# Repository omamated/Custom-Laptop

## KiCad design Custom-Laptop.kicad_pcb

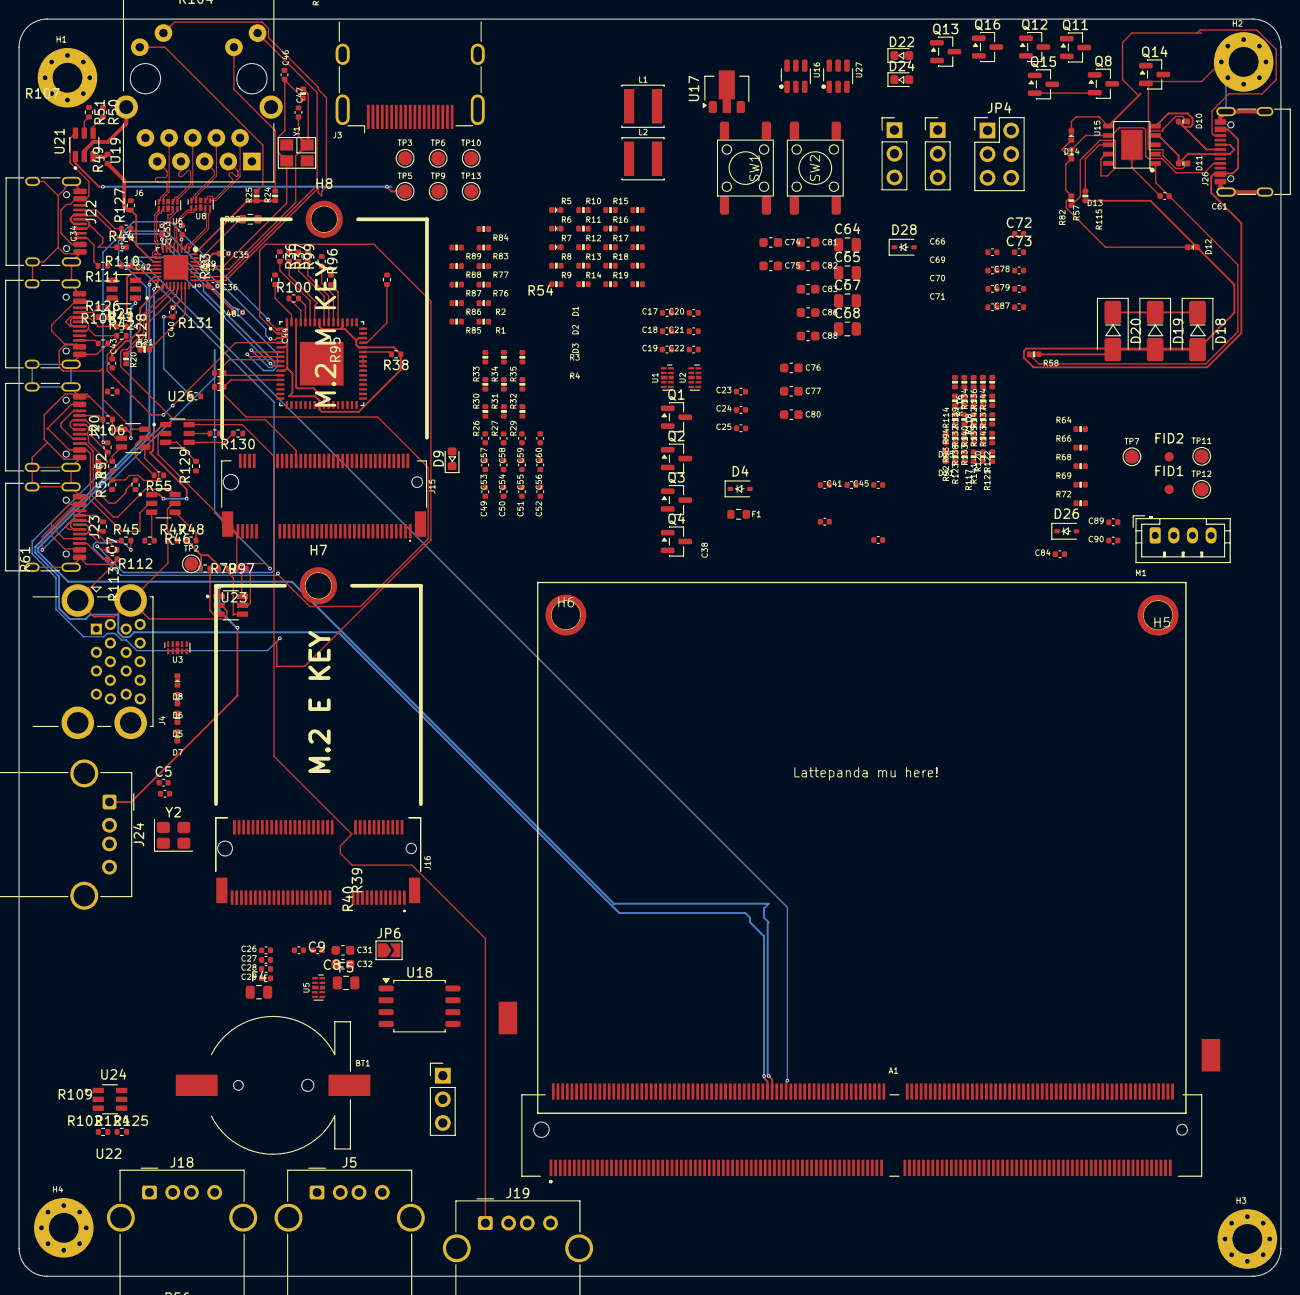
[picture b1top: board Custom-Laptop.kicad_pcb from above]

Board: 4 copper layers, 135.5 x 135.0 mm, 304 parts (0 on the bottom side), 247 nets.

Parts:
A1: LattePanda_Module_Gen1; DDR4_SODIMM_260P_8.0H_STD
BT1: Battery_Cell; Battery_Holder_CR1220_S8411-45R
C5: 1.0µF; C_0402_1005Metric
C7, C9: 27pF; C_0402_1005Metric
C8: 100nF; C_0402_1005Metric
C17, C18, C19, C20, C21, C22, C23, C24, C25, C26, C27, C28, C29, C33, C34, C35, C36, C37, C38, C39, C40, C41, C42, C43, C45, C48, C52, C54, C58, C60, C70, C71, C78, C79, C84: 100nF/16V; C_0402_1005Metric
C31, C32, C74, C75, C76, C77, C80, C81, C82, C83: 22uF/10V; C_0603_1608Metric
C44, C51, C53, C57, C59, C87, C89: 10uF/10V; C_0402_1005Metric
C46, C47, C72, C73: 12pF/50V; C_0402_1005Metric
C49, C50, C55, C56: 220nF/16V; C_0402_1005Metric
C61, C66, C69: 1uF/16V; C_0402_1005Metric
C64, C65, C67, C68: 22uF/25V; C_0805_2012Metric
C86, C88: 2.2uF/50V; C_0603_1608Metric
C90: 100nF/50V; C_0402_1005Metric
D1, D2, D3, D5, D6, D7, D8, D10, D11, D13, D14, D21, D25: 0402ESDA-05N; D_0402_1005Metric
D4, D26, D28: 1N5819WS; D_SOD-323
D9, D24: LED_G; LED_0603_1608Metric
D12: PESD24VS1UL-N; D_0402_1005Metric
D18, D19, D20: SS54; D_SMA
D22: LED_R; LED_0603_1608Metric
F1: 6V/50mA; R_0603_1608Metric
F4, F5: 6V/2A; Fuse_0805_2012Metric
FID1, FID2: Fiducial; Fiducial_1mm_Mask2mm
H1, H2, H3, H4: MountingHole_Pad; MountingHole_3.2mm_M3_Pad_Via
H5, H6: MountingHole_Pad; MountingHole_3mm_M2_Pad_TopOnly
H7, H8: MountingHole_M2.0; MountingHole_2.7mm_M2_Pad_TopOnly
J1: Conn_01x03_Pin; PinHeader_1x03_P2.54mm_Vertical
J3: HDMI_A; HDMI_A_Molex_208658-1001_Horizontal
J4: USB3_A_Stacked; USB3_A_Molex_48406-0001_Horizontal_Stacked
J5, J18, J19, J24: USB_A; USB_A_Molex_67643_Horizontal
J6: RJ45_RB1-125B8G1A; RJ45_UDE_RB1-125B8G1A
J15: Bus_M.2_Socket_M; PCIe_M.2_Connectors_P=0.5mm_H=4.2mm_KeyM
J16: Bus_M.2_Socket_E; PCIe_M.2_Connectors_P=0.5mm_H=4.2mm_KeyE
J20, J21, J22, J23: USB_C_Receptacle_USB2.0_14P; USB_C_Receptacle_HRO_TYPE-C-31-M-12
J26: USB_C_Receptacle_USB2.0; USB_C_Receptacle_G-Switch_GT-USB-7010ASV
JP1, JP5: Jumper_3_Bridged12; PinHeader_1x03_P2.54mm_Vertical
JP4: PinHeader_2x03_P2.54mm_Vertical
JP6: SolderJumper_2_Open; SolderJumper-2_P1.3mm_Open_TrianglePad1.0x1.5mm
L1, L2: 2.2uH/4.3A; L_Sunlord_SWPA4020S
M1: Fan_4pin; JST_PH_B4B-PH-K_1x04_P2.00mm_Vertical
Q1, Q8, Q11, Q12, Q13, Q14, Q15: 2N7002; SOT-23
Q2, Q3, Q4: 2SK3018; SOT-23
Q16: AO3407; SOT-23
R1, R11, R58, R92, R121, R122: 1K/1%; R_0402_1005Metric
R2, R20, R21, R34, R35, R57, R83, R115, R123, R136, R140, R143, R144: 10K/1%; R_0402_1005Metric
R3, R5, R15, R18, R19, R30, R117, R133: 2.2K/1%; R_0402_1005Metric
R4, R23, R118: 1M/1%; R_0402_1005Metric
R6, R66, R68, R137: 21.5K/1%; R_0402_1005Metric
R7, R8, R9, R10, R13, R14, R16, R17, R24, R25, R132: 470R/1%; R_0402_1005Metric
R12, R26, R27, R29, R31, R32, R33, R84, R85, R86, R87, R88, R89: 0R/1%; R_0402_1005Metric
R22: 2.49K/1%; R_0603_1608Metric
R36, R37, R39, R40, R41, R42, R43, R44, R45, R54, R61, R62, R95, R96, R98, R99: 22Ω; R_0402_1005Metric
R38, R104: 10kΩ; R_0402_1005Metric
R46, R48, R49, R50, R52, R53, R56, R79, R102, R124, R126, R127, R129, R130: 100kΩ; R_0402_1005Metric
R47, R51, R55, R97, R125, R128, R131: 16.2kΩ; R_0402_1005Metric
R64, R72, R138: 4.7K/1%; R_0402_1005Metric
R69, R93, R94, R114, R134, R139, R142: 100R/1%; R_0402_1005Metric
R76, R77, R116, R120: 100K/1%; R_0402_1005Metric
R82: 56K/1%; R_0402_1005Metric
R100: 1MΩ; R_0402_1005Metric
R101: 12kΩ ±1%; R_0402_1005Metric
R106, R107, R108, R109, R110, R111, R112, R113: 5.1kΩ; R_0402_1005Metric
R135: 75K/1%; R_0402_1005Metric
R141: 200R/1%; R_0402_1005Metric
SW1, SW2: SW_Push; SW_Push_6x6x6
TP2, TP3, TP5, TP6, TP7, TP9, TP10, TP11, TP12, TP13: TestPoint; TestPoint_Pad_D1.5mm
U1, U2: TPAZ1023-04F; Diodes_UDFN-10_1.0x2.5mm_P0.5mm
U3, U5, U7, U8: ULC0524P; Diodes_UDFN-10_1.0x2.5mm_P0.5mm
U6: RTL8111H-CG-RH; QFN-32-1EP_4x4mm_P0.4mm_EP2.65x2.65mm
U14: USB2517-JZX; QFN50P900X900X100-65N
U15: CH224K; ESSOP-10-1EP_3.9x5mm_P1.0mm_EP3.2x2.3
U16, U27: SY8253ADC; TSOT-23-6
U17: HM7533HBPR; SOT-89-3
U18: W25Q128JVS; SOIC-8_5.3x5.3mm_P1.27mm
U19, U21, U22, U23, U24, U25, U26: TPS2553DBVR; SOT95P280X145-6N
Y1: 25MHz; Crystal_SMD_3225-4Pin_3.2x2.5mm
Y2: Crystal; Crystal_SMD_3225-4Pin_3.2x2.5mm

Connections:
5V_HDMI_VCC: C25.1, D4.1 (K), F1.1, R15.1, R18.1
+1V0: C33.2, C34.2, C35.2, C36.2, C40.2, C44.2, U6.3 (AVDD10), U6.8 (AVDD10), U6.22 (DVDD10), U6.24 (REGOUT), U6.30 (AVDD10)
+1V8: C5.2, U14.25 (VDD18), U14.62 (VDD18PLL)
+3V3: C8.1, C37.2, C41.2, C45.2, C51.2, C52.2, C53.2, C54.2, C57.2, C58.2, C59.2, C60.2, C73.1, C75.2, C77.2, C79.1, C81.2, C83.2, J15.2 (3.3V), J15.4 (3.3V), J15.12 (3.3V), J15.14 (3.3V), J15.16 (3.3V), J15.18 (3.3V), J15.70 (3.3V), J15.72 (3.3V), J15.74 (3.3V), J16.2 (3.3V), J16.4 (3.3V), J16.72 (3.3V), J16.74 (3.3V), L2.2, Q1.1 (G), Q2.1 (G), Q3.1 (G), R3.1, R4.1, R5.1, R20.1, R21.1, R24.2, R25.2, R30.2, R34.2, R35.1, R38.1, R46.1, R48.1, R49.1, R50.1, R52.1, R53.1, R56.1, R64.1, R79.1, R102.1, R124.1, R126.1, R127.1, R129.1, R130.1, R137.2, R140.2, R141.1, R143.2, TP6.1 (1_1), U6.11 (AVDD33), U6.23 (VDDREG), U6.32 (AVDD33), U14.5 (VDDA33), U14.10 (VDDA33), U14.24 (VDD33CR), U14.44 (VBUS_DET), U14.46 (VDD33), U14.52 (VDDA33), U14.57 (VDDA33), U14.64 (VDD33PLL)
+3V3_ROM: C88.1, C89.2, C90.2, D28.1 (K), R2.2, R83.2, R117.2, R118.1, R120.1, R132.1, R133.2, TP13.1 (1_1), U17.3 (VOUT), U18.8 (VCC)
+5V: C31.2, C32.2, C72.1, C74.2, C76.2, C78.1, C80.2, C82.2, D4.2 (A), F4.1, F5.1, J24.1 (VBUS), L1.2, Q16.2 (S), R135.2, R144.2, TP5.1 (1_1), U19.1 (IN), U21.1 (IN), U22.1 (IN), U23.1 (IN), U24.1 (IN), U25.1 (IN), U26.1 (IN)
+5V_FAN: C84.1, D26.1 (K), M1.2 (+), Q16.3 (D), R72.1
+15V: D12.1 (K), D18.2 (A), D19.2 (A), D20.2 (A), J26.A4 (VBUS), J26.A9 (VBUS), J26.B4 (VBUS), J26.B9 (VBUS), R57.1, R58.1, TP3.1 (1_1)
+BATT: A1.115 (VBAT), R1.1
/Fan_Temp/FAN_1_PWM: A1.2 (FAN_CTL2), R64.2, R69.1, TP12.1 (1_1)
/Fan_Temp/FAN_1_TAC: A1.4 (FAN_TAC2), R66.1, R68.2, TP11.1 (1_1)
/Gigabit Ethernet/GbE_PCIe_CLK+: A1.94 (REFCLK4+), U6.15 (REFCLK_P)
/Gigabit Ethernet/GbE_PCIe_CLK-: A1.96 (REFCLK4-), U6.16 (REFCLK_N)
/Gigabit Ethernet/GbE_PCIe_RX+: A1.64 (HSIO6_RXP), C43.2
/Gigabit Ethernet/GbE_PCIe_RX-: A1.66 (HSIO6_RXN), C39.2
/Gigabit Ethernet/GbE_PCIe_TX+: A1.61 (HSIO6_TXP), C42.2
/Gigabit Ethernet/GbE_PCIe_TX-: A1.63 (HSIO6_TXN), C38.2
/Gigabit Ethernet/HSI+: C42.1, U6.13 (HSIP)
/Gigabit Ethernet/HSI-: C38.1, U6.14 (HSIN)
/Gigabit Ethernet/HSO+: C43.1, U6.17 (HSOP)
/Gigabit Ethernet/HSO-: C39.1, U6.18 (HSON)
/Gigabit Ethernet/LED1_1000: J6.L4, U6.26 (LED1)
/Gigabit Ethernet/LED2_ACT: J6.L2, U6.25 (LED2)
/Gigabit Ethernet/MDI0+: J6.R2 (TD1+), U6.1 (MDIP0), U8.5, U8.6 (NC)
/Gigabit Ethernet/MDI0-: J6.R3 (TD1-), U6.2 (MDIN0), U8.4, U8.7 (NC)
/Gigabit Ethernet/MDI1+: J6.R4 (TD2+), U6.4 (MDIP1), U8.2, U8.9 (NC)
/Gigabit Ethernet/MDI1-: J6.R5 (TD2-), U6.5 (MDIN1), U8.1, U8.10 (NC)
/Gigabit Ethernet/MDI2+: J6.R6 (TD3+), U6.6 (MDIP2), U7.5, U7.6 (NC)
/Gigabit Ethernet/MDI2-: J6.R7 (TD3-), U6.7 (MDIN2), U7.4, U7.7 (NC)
/Gigabit Ethernet/MDI3+: J6.R8 (TD4+), U6.9 (MDIP3), U7.2, U7.9 (NC)
/Gigabit Ethernet/MDI3-: J6.R9 (TD4-), U6.10 (MDIN3), U7.1, U7.10 (NC)
/Gigabit Ethernet/~CLKREQ4: A1.102 (~PCIeCLK_REQ4), U6.12 (CLKREQB)
/HDMI/DDC_SCL: D1.2 (A2), J3.15 (SCL), Q2.3 (D), R15.2
/HDMI/DDC_SDA: D3.2 (A2), J3.16 (SDA), Q3.3 (D), R18.2
/HDMI/DDI_B_DDC_SCL: A1.171 (DDC_B_SCL), Q2.2 (S), R5.2
/HDMI/DDI_B_DDC_SDA: A1.169 (DDC_B_SDA), Q3.2 (S), R3.2
/HDMI/DDI_B_HPD: A1.183 (HPD_B), Q1.2 (S), R4.2
/HDMI/DDI_B_TX0+: A1.217 (DDI_B_TX0+), C17.1
/HDMI/DDI_B_TX0-: A1.215 (DDI_B_TX0-), C18.1
/HDMI/DDI_B_TX1+: A1.211 (DDI_B_TX1+), C19.1
/HDMI/DDI_B_TX1-: A1.209 (DDI_B_TX1-), C20.1
/HDMI/DDI_B_TX2+: A1.205 (DDI_B_TX2+), C21.1
/HDMI/DDI_B_TX2-: A1.203 (DDI_B_TX2-), C22.1
/HDMI/DDI_B_TX3+: A1.199 (DDI_B_TX3+), C23.1
/HDMI/DDI_B_TX3-: A1.197 (DDI_B_TX3-), C24.1
/HDMI/HPD: D2.2 (A2), J3.19 (HPD), R11.2
/HDMI/TMDS_CK+: C23.2, J3.10 (CK+), R8.1, U2.4, U2.7 (NC)
/HDMI/TMDS_CK-: C24.2, J3.12 (CK-), R7.1, U2.5, U2.6 (NC)
/HDMI/TMDS_D0+: C21.2, J3.7 (D0+), R10.1, U2.1, U2.10 (NC)
/HDMI/TMDS_D0-: C22.2, J3.9 (D0-), R9.1, U2.2, U2.9 (NC)
/HDMI/TMDS_D1+: C19.2, J3.4 (D1+), R14.1, U1.4, U1.7 (NC)
/HDMI/TMDS_D1-: C20.2, J3.6 (D1-), R13.1, U1.5, U1.6 (NC)
/HDMI/TMDS_D2+: C17.2, J3.1 (D2+), R17.1, U1.1, U1.10 (NC)
/HDMI/TMDS_D2-: C18.2, J3.3 (D2-), R16.1, U1.2, U1.9 (NC)
/LattePanda Module/HSIO_0_TX+: A1.13 (HSIO0_TXP), C27.1
/LattePanda Module/HSIO_0_TX-: A1.15 (HSIO0_TXN), C26.1
/LattePanda Module/HSIO_1_TX+: A1.19 (HSIO1_TXP), C29.1
/LattePanda Module/HSIO_1_TX-: A1.21 (HSIO1_TXN), C28.1
/LattePanda Module/HSIO_2_RX+: A1.28 (HSIO2_RXP), J15.43 (PERp0/SATA-B-)
/LattePanda Module/HSIO_2_RX-: A1.30 (HSIO2_RXN), J15.41 (PERn0/SATA-B+)
/LattePanda Module/HSIO_2_TX+: A1.25 (HSIO2_TXP), C49.1
/LattePanda Module/HSIO_2_TX-: A1.27 (HSIO2_TXN), C50.1
/LattePanda Module/HSIO_3_RX+: A1.34 (HSIO3_RXP), J16.41 (PERp0)
/LattePanda Module/HSIO_3_RX-: A1.36 (HSIO3_RXN), J16.43 (PERn0)
/LattePanda Module/HSIO_3_TX+: A1.31 (HSIO3_TXP), C55.1
/LattePanda Module/HSIO_3_TX-: A1.33 (HSIO3_TXN), C56.1
/LattePanda Module/REFCLK0+: A1.85 (REFCLK0+), J15.53 (REFCLKn)
/LattePanda Module/REFCLK0-: A1.87 (REFCLK0-), J15.55 (REFCLKp)
/LattePanda Module/REFCLK3+: A1.88 (REFCLK3+), J16.47 (REFCLKp0)
/LattePanda Module/REFCLK3-: A1.90 (REFCLK3-), J16.49 (REFCLKn0)
/LattePanda Module/SPI_CLK: A1.155 (SPI_CLK), R85.2
/LattePanda Module/SPI_IO2: A1.161 (SPI_IO2), R88.2
/LattePanda Module/SPI_IO3: A1.153 (SPI_IO3), R89.2
/LattePanda Module/SPI_MISO/SPI_IO1: A1.163 (SPI_MISO/SPI_IO1), R87.2
/LattePanda Module/SPI_MOSI/SPI_IO0: A1.159 (SPI_MOSI/SPI_IO0), R86.2
/LattePanda Module/SUSCLK_WIFI: A1.131 (SUSCLK), R29.2, R33.2
/LattePanda Module/USB_2_P7+: A1.76 (USB2_P7), J16.3 (USB_D+)
/LattePanda Module/USB_2_P7-: A1.78 (USB2_N7), J16.5 (USB_D-)
/LattePanda Module/~CLKREQ3: A1.100 (~PCIeCLK_REQ3), R31.1
/LattePanda Module/~PWR_SW: A1.1 (~PWR_SW), JP5.1 (A), R134.1, R139.2
/LattePanda Module/~RST_SW: A1.3 (~RST_SW), R142.2
/LattePanda Module/~SPI_CS0: A1.165 (~SPI_CS0), R83.1, R84.2
/M.2 E&M Key/CON_PCIE_TX_0+: C55.2, J16.35 (PETp0)
/M.2 E&M Key/CON_PCIE_TX_0-: C56.2, J16.37 (PETn0)
/M.2 E&M Key/CON_PCIE_TX_1+: C49.2, J15.49 (PETp0/SATA-A+)
/M.2 E&M Key/CON_PCIE_TX_1-: C50.2, J15.47 (PETn0/SATA-A-)
/PSU/CC1: D13.2 (A2), J26.A5 (CC1), U15.7 (CC1)
/PSU/CC2: D14.2 (A2), J26.B5 (CC2), U15.6 (CC2)
/PSU/POWER_SW: C66.1, D21.2 (A2), JP4.4, R139.1, R140.1, SW1.1
/PSU/PWR_C_D+: D11.2 (A2), J26.A6 (D+), J26.B6 (D+), U15.4 (DP)
/PSU/PWR_C_D-: D10.2 (A2), J26.A7 (D-), J26.B7 (D-), U15.5 (DM)
/PSU/PWR_EN: Q15.1 (G), R114.2, R116.2, TP9.1 (1_1), U16.4 (EN), U27.4 (EN)
/PSU/PWR_LED: JP4.6, R141.2
/PSU/RESET_SW: C69.1, D25.2 (A2), JP4.5, R142.1, R143.1, SW2.1
/PSU/UPS_STATE_LP: R93.1, R94.1
/PSU/~SLP_S4_N: A1.7 (SLP_S4_N), JP1.3 (B), R93.2, R121.1
/USB2.0&USB3.0/CON_USB1_D_N: A1.109 (USB2_N5), J24.2 (D-)
/USB2.0&USB3.0/CON_USB1_D_P: A1.111 (USB2_P5), J24.3 (D+)
/USB2.0&USB3.0/CON_USB2_D_N: A1.79 (USB2_N3), R37.1
/USB2.0&USB3.0/CON_USB2_D_P: A1.81 (USB2_P3), R36.1
/USB2.0&USB3.0/CON_USB3_D_N: A1.73 (USB2_N2), D8.2 (A2), J4.2 (D1-)
/USB2.0&USB3.0/CON_USB3_D_P: A1.75 (USB2_P2), D7.2 (A2), J4.3 (D1+)
/USB2.0&USB3.0/CON_USB3_SSRX_N: A1.18 (HSIO0_RXN), J4.5 (SSRX1-), U5.4, U5.7 (NC)
/USB2.0&USB3.0/CON_USB3_SSRX_P: A1.16 (HSIO0_RXP), J4.6 (SSRX1+), U5.5, U5.6 (NC)
/USB2.0&USB3.0/CON_USB3_SSTX_N: C26.2, J4.8 (SSTX1-), U3.4, U3.7 (NC)
/USB2.0&USB3.0/CON_USB3_SSTX_P: C27.2, J4.9 (SSTX1+), U3.5, U3.6 (NC)
/USB2.0&USB3.0/CON_USB4_D_N: A1.67 (USB2_N1), D6.2 (A2), J4.11 (D2-)
/USB2.0&USB3.0/CON_USB4_D_P: A1.69 (USB2_P1), D5.2 (A2), J4.12 (D2+)
/USB2.0&USB3.0/CON_USB4_SSRX_N: A1.24 (HSIO1_RXN), J4.14 (SSRX2-), U5.1, U5.10 (NC)
/USB2.0&USB3.0/CON_USB4_SSRX_P: A1.22 (HSIO1_RXP), J4.15 (SSRX2+), U5.2, U5.9 (NC)
/USB2.0&USB3.0/CON_USB4_SSTX_N: C28.2, J4.17 (SSTX2-), U3.1, U3.10 (NC)
/USB2.0&USB3.0/CON_USB4_SSTX_P: C29.2, J4.18 (SSTX2+), U3.2, U3.9 (NC)
/USB2.0&USB3.0/M2: J21.A7 (D-), J21.B7 (D-), R41.1
/USB2.0&USB3.0/M3: J22.A7 (D-), J22.B7 (D-), R43.1
/USB2.0&USB3.0/M4: J23.A7 (D-), J23.B7 (D-), R45.1
/USB2.0&USB3.0/M5: J5.2 (D-), R61.1
/USB2.0&USB3.0/M6: J18.2 (D-), R95.1
/USB2.0&USB3.0/M7: J19.2 (D-), R98.1
/USB2.0&USB3.0/P2: J21.A6 (D+), J21.B6 (D+), R42.1
/USB2.0&USB3.0/P3: J22.A6 (D+), J22.B6 (D+), R44.1
/USB2.0&USB3.0/P4: J23.A6 (D+), J23.B6 (D+), R54.1
/USB2.0&USB3.0/P5: J5.3 (D+), R62.1
/USB2.0&USB3.0/P6: J18.3 (D+), R96.1
/USB2.0&USB3.0/P7: J19.3 (D+), R99.1
/USB2.0&USB3.0/XTALin: C7.1, R100.1, U14.61 (XTAL1/CLKIN), Y2.1
/USB2.0&USB3.0/XTALout: C9.1, R100.2, U14.60 (XTAL2), Y2.2
/~PLT_RST: J15.50 (~PERST), J16.52 (~PERST0), U6.19 (PERSTB)
/~PWR_LED/~PSON: A1.5 (~PWR_LED/~PSON), JP1.1 (A), R19.1, R92.1, R94.2
/~WAKE: J15.54 (~PEWAKE), J16.55 (~PEWAKE0)
GND: A1.11 (GND), A1.14 (GND), A1.17 (GND), A1.20 (GND), A1.23 (GND), A1.26 (GND), A1.29 (GND), A1.32 (GND), A1.35 (GND), A1.38 (GND), A1.41 (GND), A1.44 (GND), A1.47 (GND), A1.50 (GND), A1.53 (GND), A1.56 (GND), A1.59 (GND), A1.62 (GND), A1.65 (GND), A1.68 (GND), A1.71 (GND), A1.74 (GND), A1.77 (GND), A1.80 (GND), A1.83 (GND), A1.86 (GND), A1.89 (GND), A1.92 (GND), A1.95 (GND), A1.98 (GND), A1.101 (GND), A1.107 (GND), A1.110 (GND), A1.113 (GND), A1.116 (GND), A1.135 (GND), A1.136 (GND), A1.151 (GND), A1.158 (GND), A1.167 (GND), A1.170 (GND), A1.181 (GND), A1.182 (GND), A1.188 (GND), A1.189 (GND), A1.194 (GND), A1.195 (GND), A1.200 (GND), A1.201 (GND), A1.206 (GND), A1.207 (GND), A1.212 (GND), A1.213 (GND), A1.218 (GND), A1.219 (GND), A1.224 (GND), A1.225 (GND), A1.230 (GND), A1.231 (GND), A1.236 (GND), A1.237 (GND), A1.242 (GND), A1.243 (GND), A1.248 (GND), A1.249 (GND), A1.MP1, A1.MP2, BT1.2 (-), C5.1, C7.2, C8.2, C9.2, C25.2, C31.1, C32.1, C33.1, C34.1, C35.1, C36.1, C37.1, C40.1, C41.1, C44.1, C45.1, C46.1, C47.1, C48.2, C51.1, C52.1, C53.1, C54.1, C57.1, C58.1, C59.1, C60.1, C61.2, C64.1, C65.1, C66.2, C67.1, C68.1, C69.2, C74.1, C75.1, C76.1, C77.1, C78.2, C79.2, C80.1, C81.1, C82.1, C83.1, C84.2, C86.2, C87.2, C88.2, C89.1, C90.1, D1.1 (A1), D2.1 (A1), D3.1 (A1), D5.1 (A1), D6.1 (A1), D7.1 (A1), D8.1 (A1), D10.1 (A1), D11.1 (A1), D12.2 (A), D13.1 (A1), D14.1 (A1), D21.1 (A1), D25.1 (A1), H1.1 (1_1), H2.1 (1_1), H3.1 (1_1), H4.1 (1_1), H5.1 (1_1), H6.1 (1_1), H7.1 (1_1), H8.1 (1_1), J1.3, J3.2 (D2S), J3.5 (D1S), J3.8 (D0S), J3.11 (CKS), J3.17 (GND), J3.SH, J4.4 (GND1), J4.7 (DRAIN1), J4.13 (GND2), J4.16 (DRAIN2), J4.19 (SHIELD), J5.4 (GND), J5.SH (Shield), J6.R10 (GND), J6.SH, J15.1 (GND), J15.3 (GND), J15.9 (GND), J15.15 (GND), J15.21 (GND), J15.27 (GND), J15.33 (GND), J15.39 (GND), J15.45 (GND), J15.51 (GND), J15.57 (GND), J15.71 (GND), J15.73 (GND), J15.75 (GND), J15.MP1, J15.MP2, J16.1 (GND), J16.7 (GND), J16.18 (GND), J16.33 (GND), J16.39 (GND), J16.45 (GND), J16.51 (GND), J16.57 (GND), J16.63 (GND), J16.69 (GND), J16.75 (GND), J16.MP1, J16.MP2, J18.4 (GND), J18.SH (Shield), J19.4 (GND), J19.SH (Shield), J20.A1 (GND), J20.A12 (GND), J20.B1 (GND), J20.B12 (GND), J20.SH (SHIELD), J21.A1 (GND), J21.A12 (GND), J21.B1 (GND), J21.B12 (GND), J21.SH (SHIELD), J22.A1 (GND), J22.A12 (GND), J22.B1 (GND), J22.B12 (GND), J22.SH (SHIELD), J23.A1 (GND), J23.A12 (GND), J23.B1 (GND), J23.B12 (GND), J23.SH (SHIELD), J24.4 (GND), J24.SH (Shield), J26.A1 (GND), J26.A12 (GND), J26.B1 (GND), J26.B12 (GND), J26.S1 (SHIELD), JP4.1, JP4.2, JP4.3, JP6.1 (A), M1.1 (-), Q4.2 (S), Q8.2 (S), Q12.2 (S), Q13.2 (S), Q14.2 (S), Q15.2 (S), R6.2, R12.2, R22.1, R27.2, R32.2, R47.1, R51.1, R55.1, R66.2, R76.2, R77.2, R82.2, R97.1, R101.1, R104.1, R106.1, R107.1, R108.1, R109.1, R110.1, R111.1, R112.1, R113.1, R115.1, R116.1, R123.1, R125.1, R128.1, R131.1, R132.2, R136.1, R138.1, SW1.2, SW2.2, U1.3 (VSS), U1.8 (VSS), U2.3 (VSS), U2.8 (VSS), U3.3 (VSS), U3.8 (VSS), U5.3 (VSS), U5.8 (VSS), U6.33 (GND), U7.3 (VSS), U7.8 (VSS), U8.3 (VSS), U8.8 (VSS), U14.13 (CFG_SEL2), U14.19 (TEST), U14.40 (SDA/SMBDATA/NON_REM1), U14.41 (SCL/SMBCLK/CFG_SEL0), U14.42 (HS_IND/CFG_SEL1), U14.65 (VSS), U15.0 (GND), U16.2 (GND), U17.1 (GND), U18.4 (GND), U19.2 (GND), U21.2 (GND), U22.2 (GND), U23.2 (GND), U24.2 (GND), U25.2 (GND), U26.2 (GND), U27.2 (GND), Y1.2, Y1.4
unnamed: A1.187 (HPD_0), R76.1
unnamed: A1.185 (HPD_1), R77.1
unnamed: A1.12 (SIO_UART_RX), J1.2
unnamed: A1.10 (SIO_UART_TX), J1.1
unnamed: A1.133 (~BIOS_SEL), JP6.2 (B), R2.1, TP7.1 (1_1)
unnamed: BT1.1 (+), R1.2
unnamed: D9.2 (A), R30.1
unnamed: D9.1 (K), J15.10 (DAS/~DSS/~LED1)
unnamed: D22.2 (A), R117.1
unnamed: D22.1 (K), Q8.3 (D), R122.1
unnamed: D24.2 (A), R133.1
unnamed: D24.1 (K), Q11.3 (D)
unnamed: D26.2 (A), M1.3 (Tacho), R68.1, R72.2
unnamed: C87.1, D28.2 (A), Q13.1 (G), R118.2
unnamed: F1.2, J3.18 (+5V)
unnamed: F4.2, J4.1 (VBUS1)
unnamed: F5.2, J4.10 (VBUS2)
unnamed: J5.1 (VBUS), U24.6 (OUT)
unnamed: C48.1, J6.R1 (CT)
unnamed: J6.L1, R25.1
unnamed: J6.L3, R24.1
unnamed: J15.38 (DEVSLP), TP2.1 (1_1)
unnamed: J15.68 (SUSCLK), R29.1
unnamed: J15.52 (~CLKREQ), R26.2, R27.1
unnamed: J16.50 (SUSCLK), R33.1
unnamed: J16.53 (~CLKREQ0), R31.2, R32.1
unnamed: J16.56 (~W_DISABLE1), R34.1
unnamed: J16.54 (~W_DISABLE2), R35.2
unnamed: J18.1 (VBUS), U25.6 (OUT)
unnamed: J19.1 (VBUS), U26.6 (OUT)
unnamed: J20.A5 (CC1), R106.2
unnamed: J20.B5 (CC2), R107.2
unnamed: J20.A6 (D+), J20.B6 (D+), R40.1
unnamed: J20.A7 (D-), J20.B7 (D-), R39.1
unnamed: J21.A5 (CC1), R108.2
unnamed: J21.B5 (CC2), R109.2
unnamed: J22.A5 (CC1), R110.2
unnamed: J22.B5 (CC2), R111.2
unnamed: J23.A5 (CC1), R112.2
unnamed: J23.B5 (CC2), R113.2
unnamed: JP1.2 (C), R114.1
unnamed: JP5.2 (C), Q12.3 (D)
unnamed: M1.4 (PWM), R69.2
unnamed: Q1.3 (D), R6.1, R11.1
unnamed: Q4.3 (D), R7.2, R8.2, R9.2, R10.2, R12.1, R13.2, R14.2, R16.2, R17.2
unnamed: Q4.1 (G), R19.2
unnamed: Q8.1 (G), R92.2, R115.2
unnamed: Q11.1 (G), R121.2, R123.2
unnamed: Q11.2 (S), Q14.3 (D)
unnamed: Q12.1 (G), Q13.3 (D), R120.2
unnamed: Q14.1 (G), R122.2
unnamed: Q15.3 (D), Q16.1 (G), R144.1
unnamed: C47.2, R23.2, U6.28 (CKXTAL1), Y1.1
unnamed: C46.2, R23.1, U6.29 (CKXTAL2), Y1.3
unnamed: R20.2, U6.20 (ISOLATEB)
unnamed: R21.2, U6.21 (LANWAKEB)
unnamed: R22.2, U6.31 (RSET)
unnamed: R101.2, U14.63 (RBIAS)
unnamed: R104.2, U14.45 (SUSP_IND/LOCAL_PWR/NON_REM0)
unnamed: R39.2, U14.1 (USBDN1_DM/PRT_DIS_M1)
unnamed: R40.2, U14.2 (USBDN1_DP/PRT_DIS_P1)
unnamed: R41.2, U14.3 (USBDN2_DM/PRT_DIS_M2)
unnamed: R42.2, U14.4 (USBDN2_DP/PRT_DIS_P2)
unnamed: R43.2, U14.6 (USBDN3_DM/PRT_DIS_M3)
unnamed: R44.2, U14.7 (USBDN3_DP/PRT_DIS_P3)
unnamed: R45.2, U14.8 (USBDN4_DM/PRT_DIS_M4)
unnamed: R54.2, U14.9 (USBDN4_DP/PRT_DIS_P4)
unnamed: R61.2, U14.11 (USBDN5_DM/PRT_DIS_M5)
unnamed: R62.2, U14.12 (USBDN5_DP/PRT_DIS_P5)
unnamed: R95.2, U14.53 (USBDN6_DM/PRT_DIS_M6)
unnamed: R96.2, U14.54 (USBDN6_DP/PRT_DIS_P6)
unnamed: R98.2, U14.55 (USBDN7_DM/PRT_DIS_M7)
unnamed: R99.2, U14.56 (USBDN7_DP/PRT_DIS_P7)
unnamed: R37.2, U14.58 (USBUP_DM)
unnamed: R36.2, U14.59 (USBUP_DP)
unnamed: R38.2, U14.43 (~RESET)
unnamed: R82.1, U15.9 (CFG1)
unnamed: R57.2, U15.8 (VBUS)
unnamed: C61.1, R58.2, U15.1 (VDD)
unnamed: C70.2, U16.1 (BOOST)
unnamed: C72.2, R135.1, R136.2, U16.3 (FB)
unnamed: C70.1, L1.1, U16.6 (SW)
unnamed: R85.1, U18.6 (CLK)
unnamed: R86.1, U18.5 (DI(IO0))
unnamed: R87.1, U18.2 (DO(IO1))
unnamed: R88.1, U18.3 (IO2)
unnamed: R89.1, U18.7 (IO3)
unnamed: R84.1, U18.1 (~CS)
unnamed: R46.2, U19.3 (EN)
unnamed: R47.2, U19.5 (ILIM)
unnamed: J20.A4 (VBUS), J20.A9 (VBUS), J20.B4 (VBUS), J20.B9 (VBUS), U19.6 (OUT)
unnamed: R48.2, U19.4 (~FAULT)
unnamed: R49.2, U21.3 (EN)
unnamed: R51.2, U21.5 (ILIM)
unnamed: J22.A4 (VBUS), J22.A9 (VBUS), J22.B4 (VBUS), J22.B9 (VBUS), U21.6 (OUT)
unnamed: R50.2, U21.4 (~FAULT)
unnamed: R52.2, U22.3 (EN)
unnamed: R55.2, U22.5 (ILIM)
unnamed: J21.A4 (VBUS), J21.A9 (VBUS), J21.B4 (VBUS), J21.B9 (VBUS), U22.6 (OUT)
unnamed: R53.2, U22.4 (~FAULT)
unnamed: R56.2, U23.3 (EN)
unnamed: R97.2, U23.5 (ILIM)
unnamed: J23.A4 (VBUS), J23.A9 (VBUS), J23.B4 (VBUS), J23.B9 (VBUS), U23.6 (OUT)
unnamed: R79.2, U23.4 (~FAULT)
unnamed: R102.2, U24.3 (EN)
unnamed: R125.2, U24.5 (ILIM)
unnamed: R124.2, U24.4 (~FAULT)
unnamed: R126.2, U25.3 (EN)
unnamed: R128.2, U25.5 (ILIM)
unnamed: R127.2, U25.4 (~FAULT)
unnamed: R129.2, U26.3 (EN)
unnamed: R131.2, U26.5 (ILIM)
unnamed: R130.2, U26.4 (~FAULT)
unnamed: C71.2, U27.1 (BOOST)
unnamed: C73.2, R137.1, R138.2, U27.3 (FB)
unnamed: C71.1, L2.1, U27.6 (SW)
VDC: A1.250 (VIN), A1.251 (VIN), A1.252 (VIN), A1.253 (VIN), A1.254 (VIN), A1.255 (VIN), A1.256 (VIN), A1.257 (VIN), A1.258 (VIN), A1.259 (VIN), A1.260 (VIN), C64.2, C65.2, C67.2, C68.2, C86.1, D18.1 (K), D19.1 (K), D20.1 (K), TP10.1 (1_1), U16.5 (VIN), U17.2 (VIN), U27.5 (VIN)
